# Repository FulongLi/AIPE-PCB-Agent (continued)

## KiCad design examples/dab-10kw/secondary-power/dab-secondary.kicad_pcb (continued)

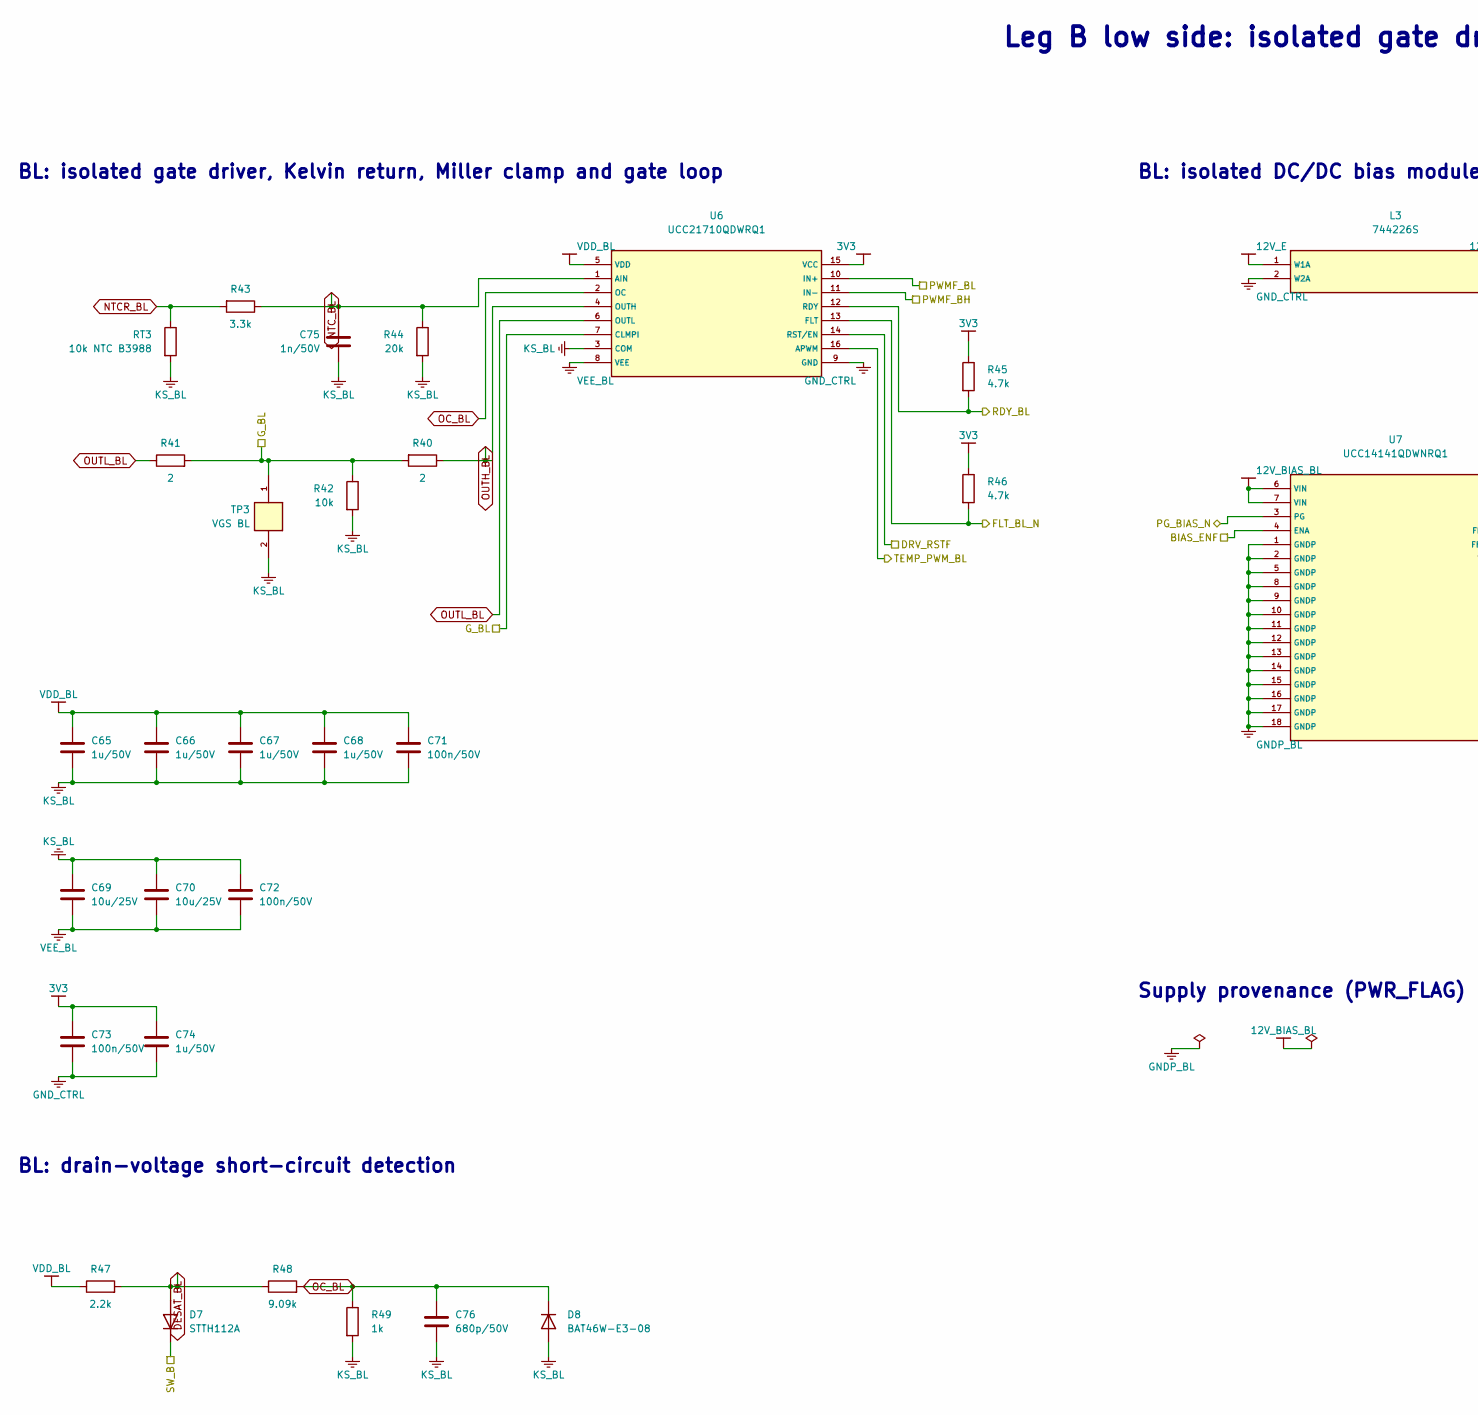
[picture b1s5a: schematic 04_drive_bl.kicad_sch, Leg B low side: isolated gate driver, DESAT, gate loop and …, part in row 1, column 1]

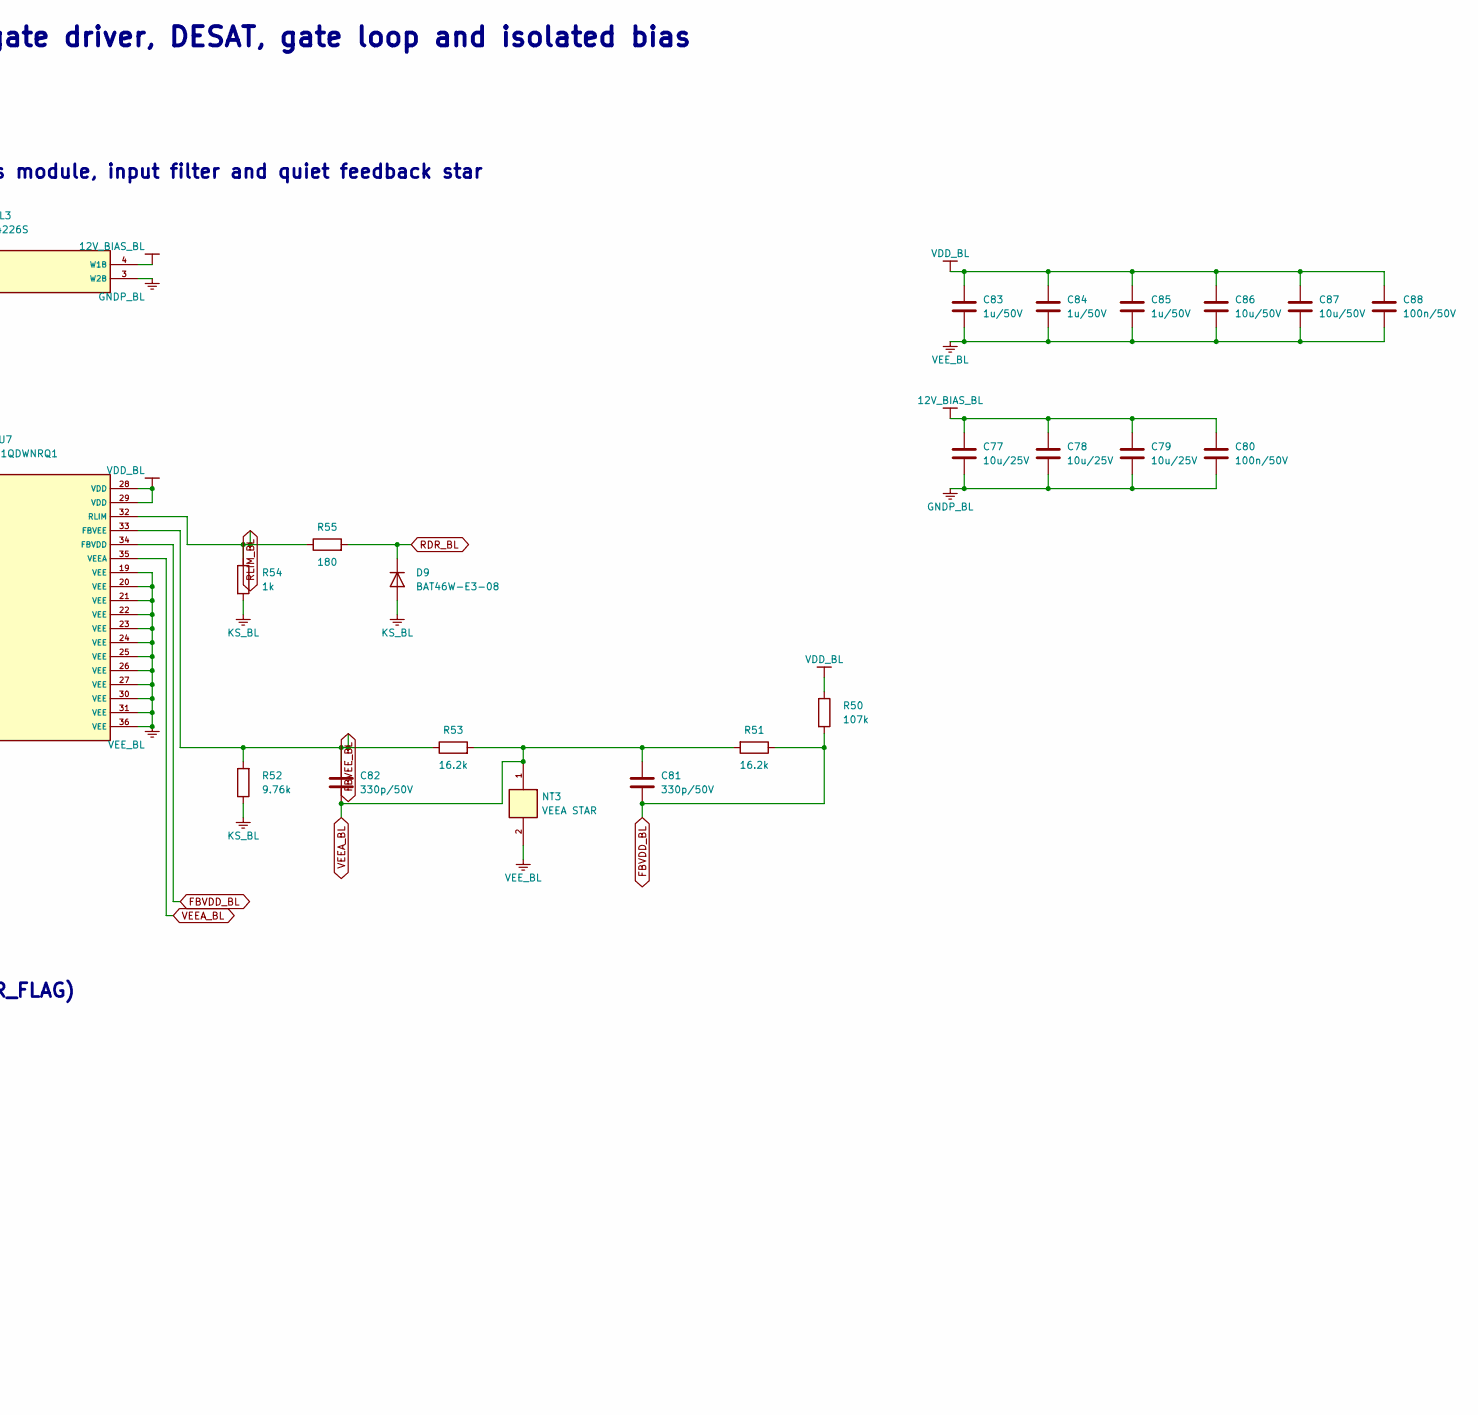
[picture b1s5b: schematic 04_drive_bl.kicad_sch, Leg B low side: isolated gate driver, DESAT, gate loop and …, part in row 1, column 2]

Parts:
C65, C66, C67, C68, C74, C83, C84, C85: 1u/50V; C_0805_2012Metric
C69, C70, C77, C78, C79: 10u/25V; C_1210_3225Metric
C71, C72, C73, C80, C88: 100n/50V; C_0603_1608Metric
C75: 1n/50V; C_0603_1608Metric
C76: 680p/50V; C_0603_1608Metric
C81, C82: 330p/50V; C_0603_1608Metric
C86, C87: 10u/50V; C_1210_3225Metric
D7: STTH112A; D_DO-41_SOD81_P10.16mm_Horizontal
D8, D9: BAT46W-E3-08; D_SOD-123
L3: 744226S; L_CommonMode_Wuerth_WE-SL2
NT3: VEEA STAR; NetTie-2_SMD_Pad0.5mm
R40, R41: 2; R_1206_3216Metric
R42: 10k; R_0805_2012Metric
R43: 3.3k; R_0603_1608Metric
R44: 20k; R_0603_1608Metric
R45, R46: 4.7k; R_0603_1608Metric
R47: 2.2k; R_1206_3216Metric
R48: 9.09k; R_0603_1608Metric
R49: 1k; R_0603_1608Metric
R50: 107k; R_0603_1608Metric
R51, R53: 16.2k; R_0603_1608Metric
R52: 9.76k; R_0603_1608Metric
R54: 1k; R_1206_3216Metric
R55: 180; R_1206_3216Metric
RT3: 10k NTC B3988; R_0805_2012Metric
TP3: VGS BL; TestPoint_2Pads_Pitch2.54mm_Drill0.8mm
U6: UCC21710QDWRQ1; DAB_UCC21710_DW_HV
U7: UCC14141QDWNRQ1; DAB_UCC14141_DWN

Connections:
3V3: C73.1, C74.1, R45.1, R46.1, U6.15 (VCC); also elsewhere on the board
12V_BIAS_BL: C77.1, C78.1, C79.1, C80.1, L3.4 (W1B), U7.6 (VIN), U7.7 (VIN)
12V_E: L3.1 (W1A); also elsewhere on the board
BIAS_ENF: U7.4 (ENA); also elsewhere on the board
DESAT_BL: D7.2 (A), R47.2, R48.1
DRV_RSTF: U6.14 (RST/EN); also elsewhere on the board
FBVDD_BL: C81.1, R50.2, R51.1, U7.34 (FBVDD)
FBVEE_BL: C82.1, R52.2, R53.1, U7.33 (FBVEE)
FLT_BL_N: R46.2, U6.13 (FLT); also elsewhere on the board
GNDP_BL: C77.2, C78.2, C79.2, C80.2, L3.3 (W2B), U7.1 (GNDP), U7.2 (GNDP), U7.5 (GNDP), U7.8 (GNDP), U7.9 (GNDP), U7.10 (GNDP), U7.11 (GNDP), U7.12 (GNDP), U7.13 (GNDP), U7.14 (GNDP), U7.15 (GNDP), U7.16 (GNDP), U7.17 (GNDP), U7.18 (GNDP)
GND_CTRL: C73.2, C74.2, L3.2 (W2A), U6.9 (GND); also elsewhere on the board
G_BL: R40.2, R41.2, R42.1, TP3.1, U6.7 (CLMPI); also elsewhere on the board
KS_BL: C65.2, C66.2, C67.2, C68.2, C69.1, C70.1, C71.2, C72.1, C75.2, C76.2, D8.2 (A), D9.2 (A), R42.2, R44.2, R49.2, R52.1, R54.2, RT3.2, TP3.2, U6.3 (COM); also elsewhere on the board
NTCR_BL: R43.2, RT3.1
NTC_BL: C75.1, R43.1, R44.1, U6.1 (AIN)
OC_BL: C76.1, D8.1 (K), R48.2, R49.1, U6.2 (OC)
OUTH_BL: R40.1, U6.4 (OUTH)
OUTL_BL: R41.1, U6.6 (OUTL)
PG_BIAS_N: U7.3 (PG); also elsewhere on the board
PWMF_BH: U6.11 (IN-); also elsewhere on the board
PWMF_BL: U6.10 (IN+); also elsewhere on the board
RDR_BL: D9.1 (K), R55.2
RDY_BL: R45.2, U6.12 (RDY); also elsewhere on the board
RLIM_BL: R54.1, R55.1, U7.32 (RLIM)
SW_B: D7.1 (K); also elsewhere on the board
TEMP_PWM_BL: U6.16 (APWM); also elsewhere on the board
VDD_BL: C65.1, C66.1, C67.1, C68.1, C71.1, C83.1, C84.1, C85.1, C86.1, C87.1, C88.1, R47.1, R50.1, U6.5 (VDD), U7.28 (VDD), U7.29 (VDD)
VEEA_BL: C81.2, C82.2, NT3.1, R51.2, R53.2, U7.35 (VEEA)
VEE_BL: C69.2, C70.2, C72.2, C83.2, C84.2, C85.2, C86.2, C87.2, C88.2, NT3.2, U6.8 (VEE), U7.19 (VEE), U7.20 (VEE), U7.21 (VEE), U7.22 (VEE), U7.23 (VEE), U7.24 (VEE), U7.25 (VEE), U7.26 (VEE), U7.27 (VEE), U7.30 (VEE), U7.31 (VEE), U7.36 (VEE)

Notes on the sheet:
Leg B low side: isolated gate driver, DESAT, gate loop and isolated bias
BL: isolated gate driver, Kelvin return, Miller clamp and gate loop
BL: drain-voltage short-circuit detection
BL: isolated DC/DC bias module, input filter and quiet feedback star
Supply provenance (PWR_FLAG)

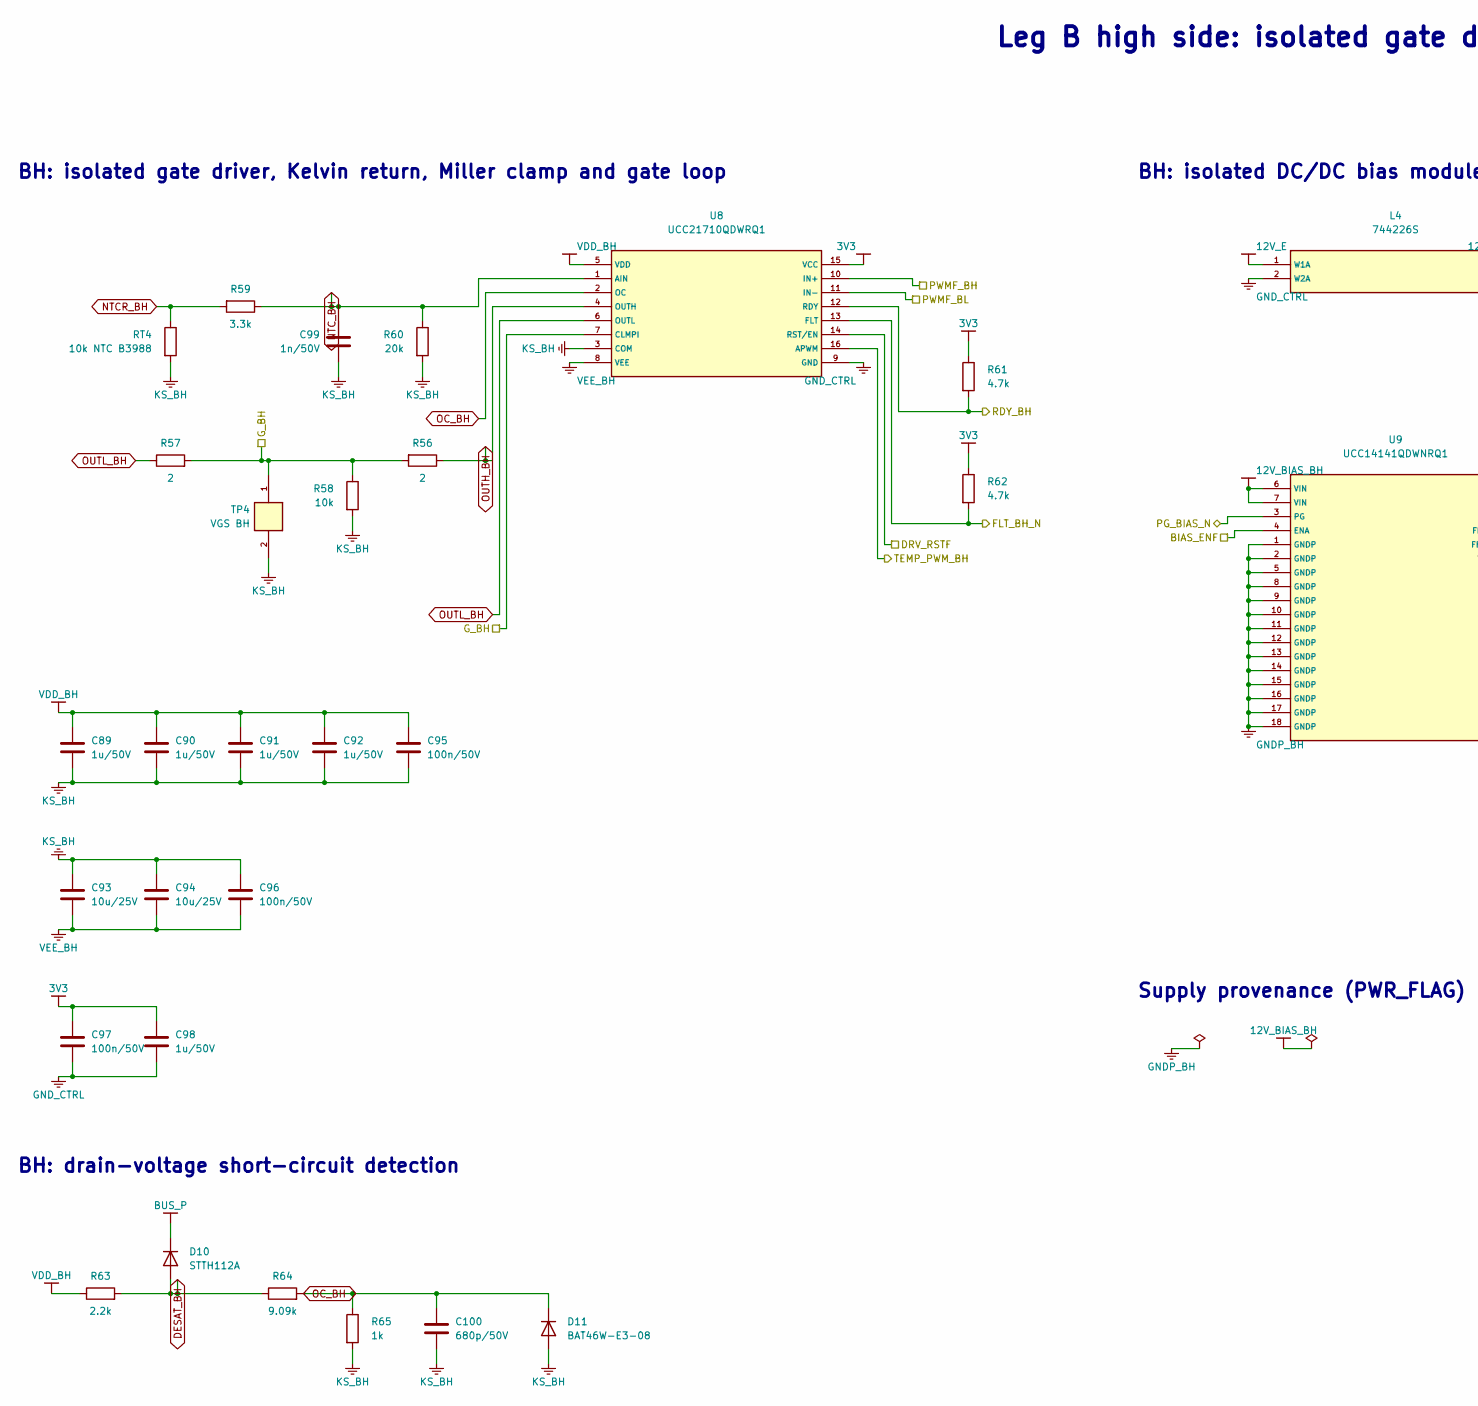
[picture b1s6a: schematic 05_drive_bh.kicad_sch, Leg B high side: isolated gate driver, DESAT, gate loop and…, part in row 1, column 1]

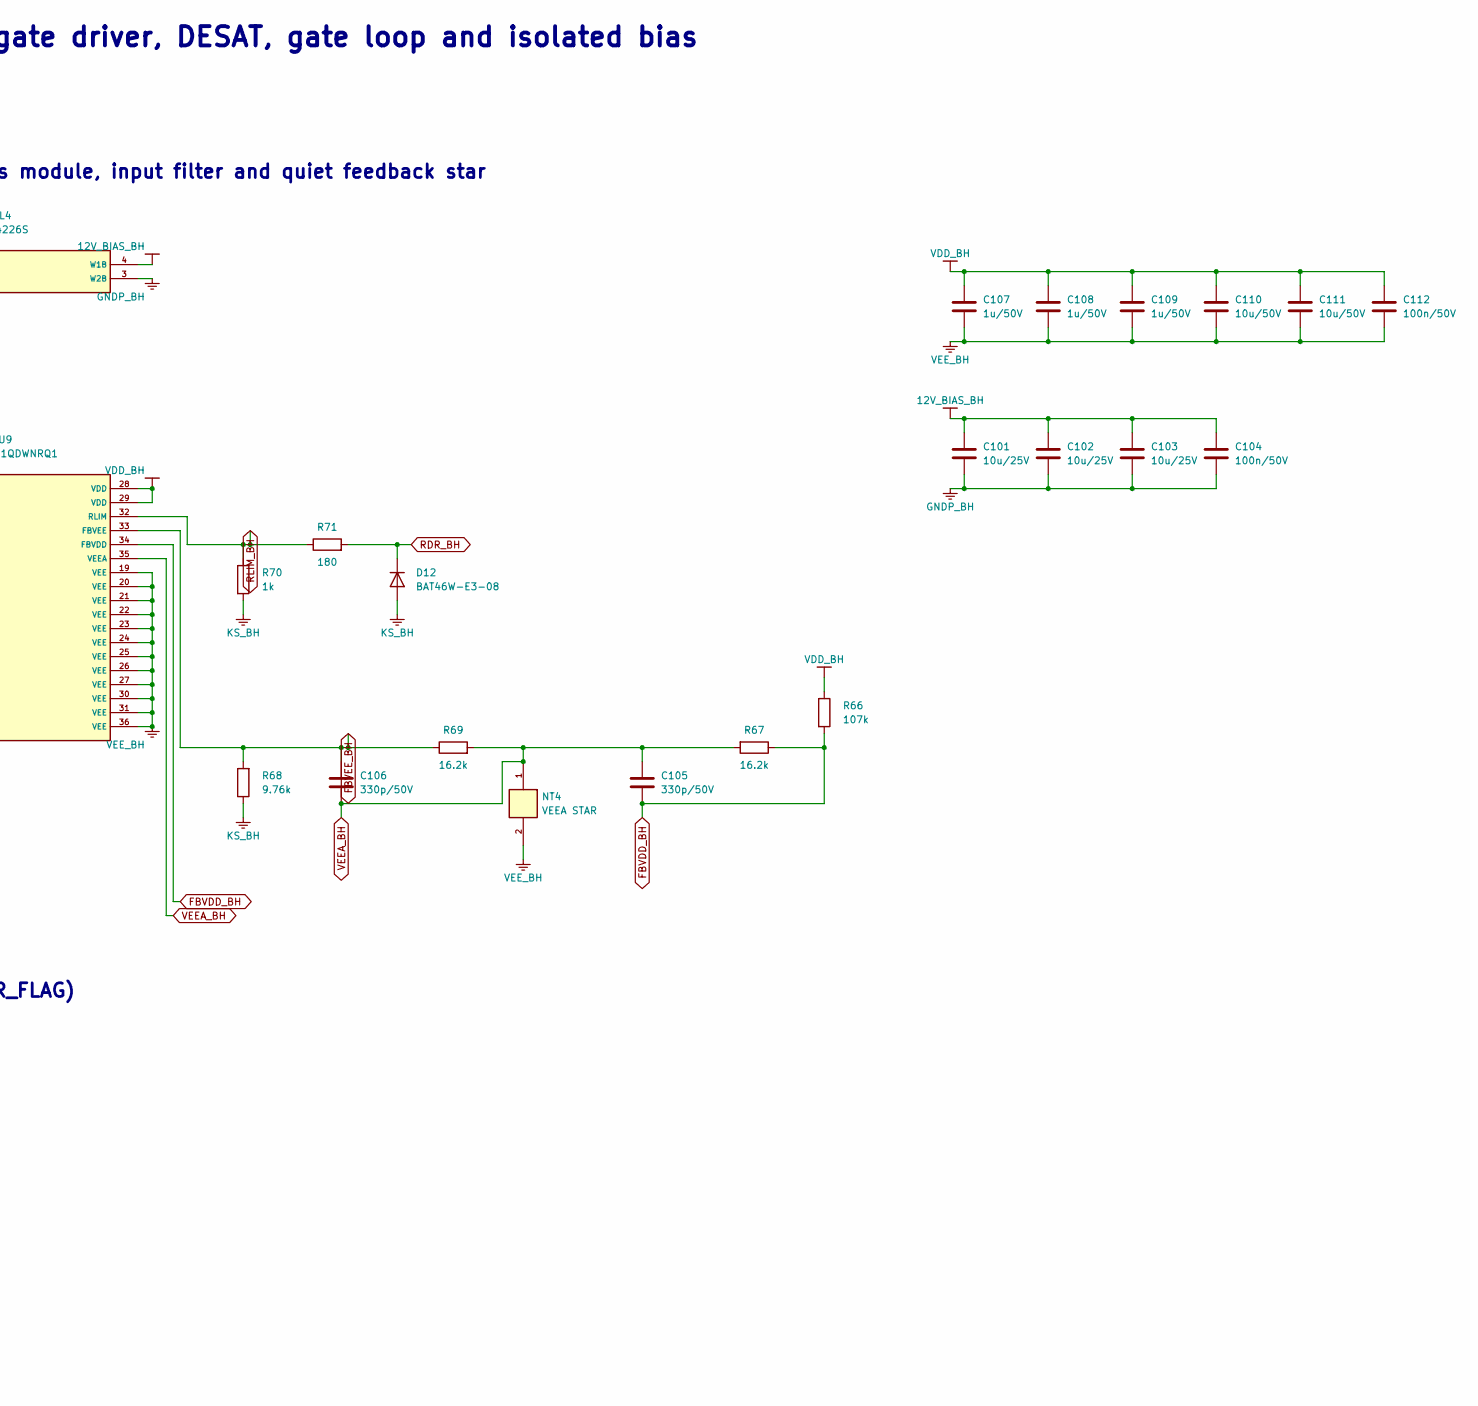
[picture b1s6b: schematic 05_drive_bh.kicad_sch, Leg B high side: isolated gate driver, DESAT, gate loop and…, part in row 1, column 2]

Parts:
C89, C90, C91, C92, C98, C107, C108, C109: 1u/50V; C_0805_2012Metric
C93, C94, C101, C102, C103: 10u/25V; C_1210_3225Metric
C95, C96, C97, C104, C112: 100n/50V; C_0603_1608Metric
C99: 1n/50V; C_0603_1608Metric
C100: 680p/50V; C_0603_1608Metric
C105, C106: 330p/50V; C_0603_1608Metric
C110, C111: 10u/50V; C_1210_3225Metric
D10: STTH112A; D_DO-41_SOD81_P10.16mm_Horizontal
D11, D12: BAT46W-E3-08; D_SOD-123
L4: 744226S; L_CommonMode_Wuerth_WE-SL2
NT4: VEEA STAR; NetTie-2_SMD_Pad0.5mm
R56, R57: 2; R_1206_3216Metric
R58: 10k; R_0805_2012Metric
R59: 3.3k; R_0603_1608Metric
R60: 20k; R_0603_1608Metric
R61, R62: 4.7k; R_0603_1608Metric
R63: 2.2k; R_1206_3216Metric
R64: 9.09k; R_0603_1608Metric
R65: 1k; R_0603_1608Metric
R66: 107k; R_0603_1608Metric
R67, R69: 16.2k; R_0603_1608Metric
R68: 9.76k; R_0603_1608Metric
R70: 1k; R_1206_3216Metric
R71: 180; R_1206_3216Metric
RT4: 10k NTC B3988; R_0805_2012Metric
TP4: VGS BH; TestPoint_2Pads_Pitch2.54mm_Drill0.8mm
U8: UCC21710QDWRQ1; DAB_UCC21710_DW_HV
U9: UCC14141QDWNRQ1; DAB_UCC14141_DWN

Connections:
3V3: C97.1, C98.1, R61.1, R62.1, U8.15 (VCC); also elsewhere on the board
12V_BIAS_BH: C101.1, C102.1, C103.1, C104.1, L4.4 (W1B), U9.6 (VIN), U9.7 (VIN)
12V_E: L4.1 (W1A); also elsewhere on the board
BIAS_ENF: U9.4 (ENA); also elsewhere on the board
BUS_P: D10.1 (K); also elsewhere on the board
DESAT_BH: D10.2 (A), R63.2, R64.1
DRV_RSTF: U8.14 (RST/EN); also elsewhere on the board
FBVDD_BH: C105.1, R66.2, R67.1, U9.34 (FBVDD)
FBVEE_BH: C106.1, R68.2, R69.1, U9.33 (FBVEE)
FLT_BH_N: R62.2, U8.13 (FLT); also elsewhere on the board
GNDP_BH: C101.2, C102.2, C103.2, C104.2, L4.3 (W2B), U9.1 (GNDP), U9.2 (GNDP), U9.5 (GNDP), U9.8 (GNDP), U9.9 (GNDP), U9.10 (GNDP), U9.11 (GNDP), U9.12 (GNDP), U9.13 (GNDP), U9.14 (GNDP), U9.15 (GNDP), U9.16 (GNDP), U9.17 (GNDP), U9.18 (GNDP)
GND_CTRL: C97.2, C98.2, L4.2 (W2A), U8.9 (GND); also elsewhere on the board
G_BH: R56.2, R57.2, R58.1, TP4.1, U8.7 (CLMPI); also elsewhere on the board
KS_BH: C89.2, C90.2, C91.2, C92.2, C93.1, C94.1, C95.2, C96.1, C99.2, C100.2, D11.2 (A), D12.2 (A), R58.2, R60.2, R65.2, R68.1, R70.2, RT4.2, TP4.2, U8.3 (COM); also elsewhere on the board
NTCR_BH: R59.2, RT4.1
NTC_BH: C99.1, R59.1, R60.1, U8.1 (AIN)
OC_BH: C100.1, D11.1 (K), R64.2, R65.1, U8.2 (OC)
OUTH_BH: R56.1, U8.4 (OUTH)
OUTL_BH: R57.1, U8.6 (OUTL)
PG_BIAS_N: U9.3 (PG); also elsewhere on the board
PWMF_BH: U8.10 (IN+); also elsewhere on the board
PWMF_BL: U8.11 (IN-); also elsewhere on the board
RDR_BH: D12.1 (K), R71.2
RDY_BH: R61.2, U8.12 (RDY); also elsewhere on the board
RLIM_BH: R70.1, R71.1, U9.32 (RLIM)
TEMP_PWM_BH: U8.16 (APWM); also elsewhere on the board
VDD_BH: C89.1, C90.1, C91.1, C92.1, C95.1, C107.1, C108.1, C109.1, C110.1, C111.1, C112.1, R63.1, R66.1, U8.5 (VDD), U9.28 (VDD), U9.29 (VDD)
VEEA_BH: C105.2, C106.2, NT4.1, R67.2, R69.2, U9.35 (VEEA)
VEE_BH: C93.2, C94.2, C96.2, C107.2, C108.2, C109.2, C110.2, C111.2, C112.2, NT4.2, U8.8 (VEE), U9.19 (VEE), U9.20 (VEE), U9.21 (VEE), U9.22 (VEE), U9.23 (VEE), U9.24 (VEE), U9.25 (VEE), U9.26 (VEE), U9.27 (VEE), U9.30 (VEE), U9.31 (VEE), U9.36 (VEE)

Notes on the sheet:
Leg B high side: isolated gate driver, DESAT, gate loop and isolated bias
BH: isolated gate driver, Kelvin return, Miller clamp and gate loop
BH: drain-voltage short-circuit detection
BH: isolated DC/DC bias module, input filter and quiet feedback star
Supply provenance (PWR_FLAG)

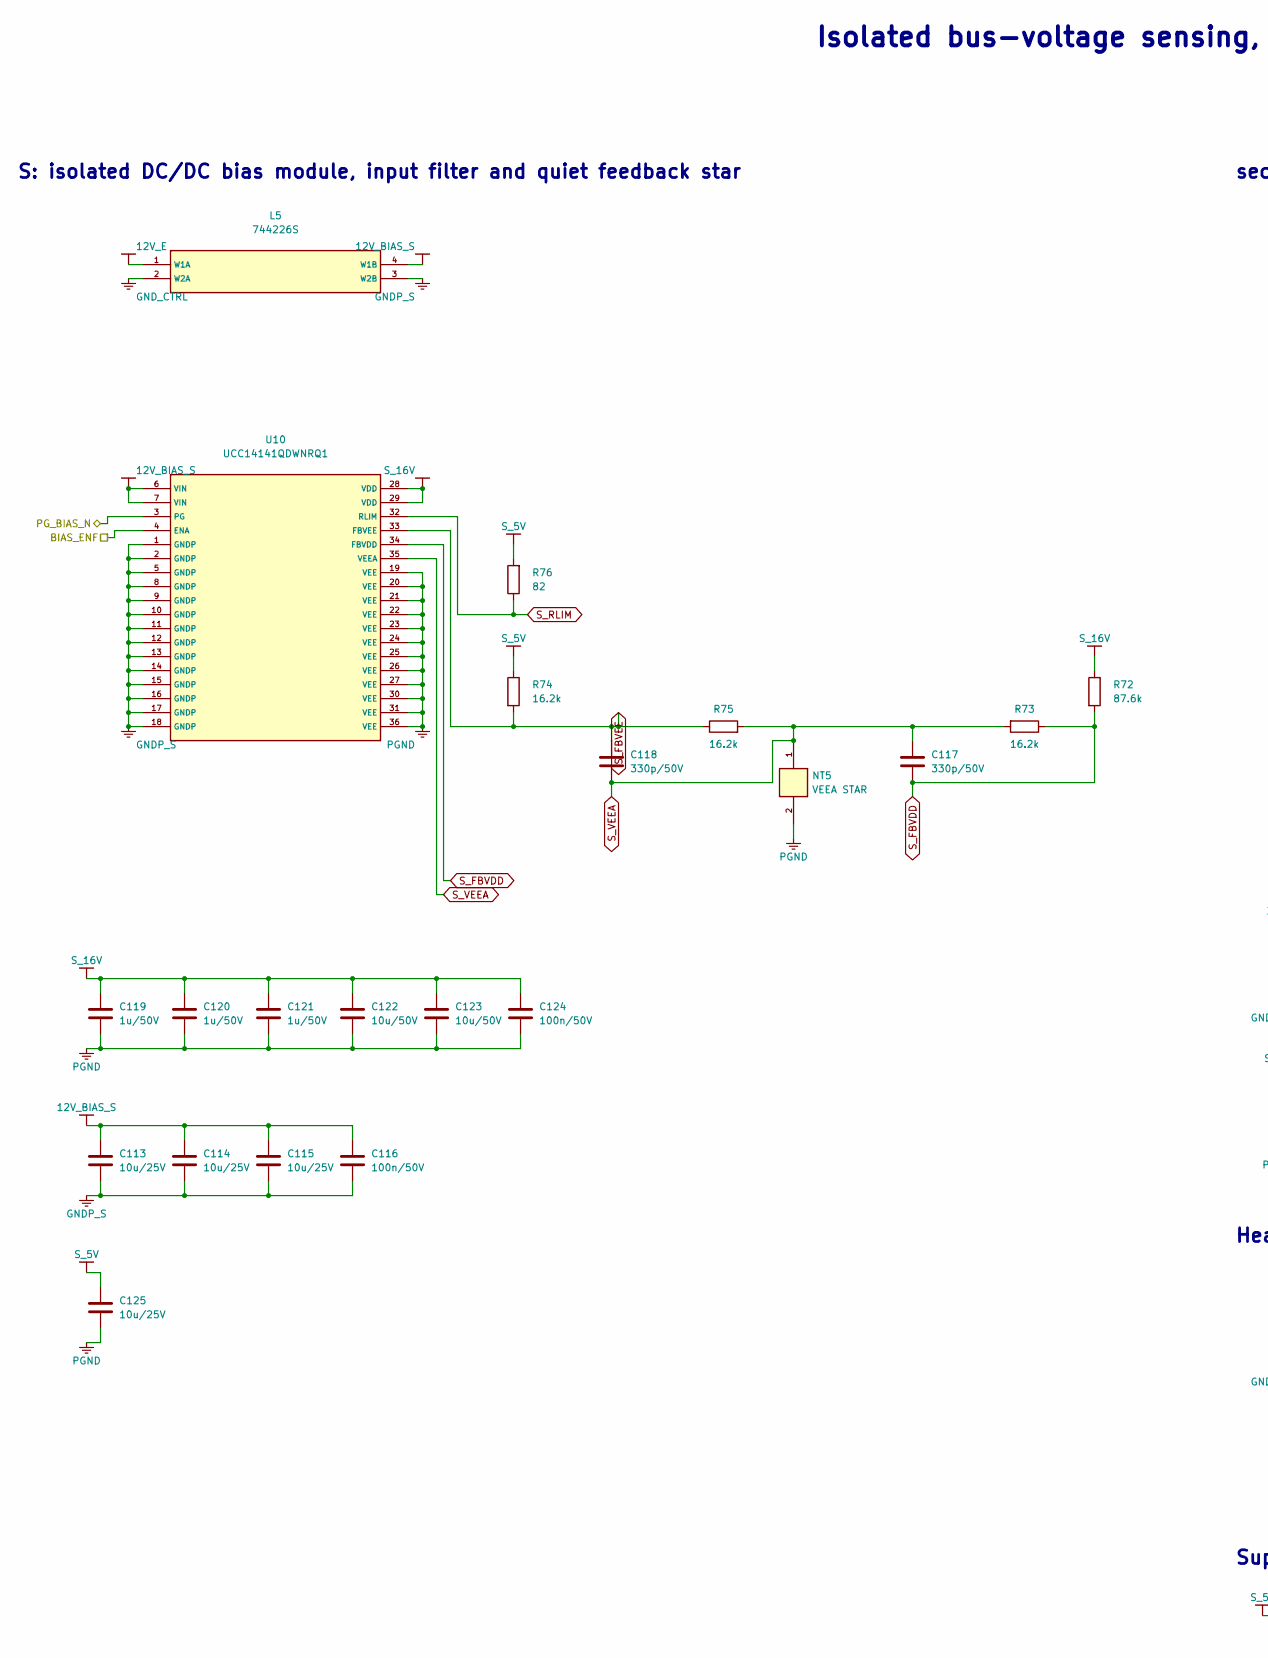
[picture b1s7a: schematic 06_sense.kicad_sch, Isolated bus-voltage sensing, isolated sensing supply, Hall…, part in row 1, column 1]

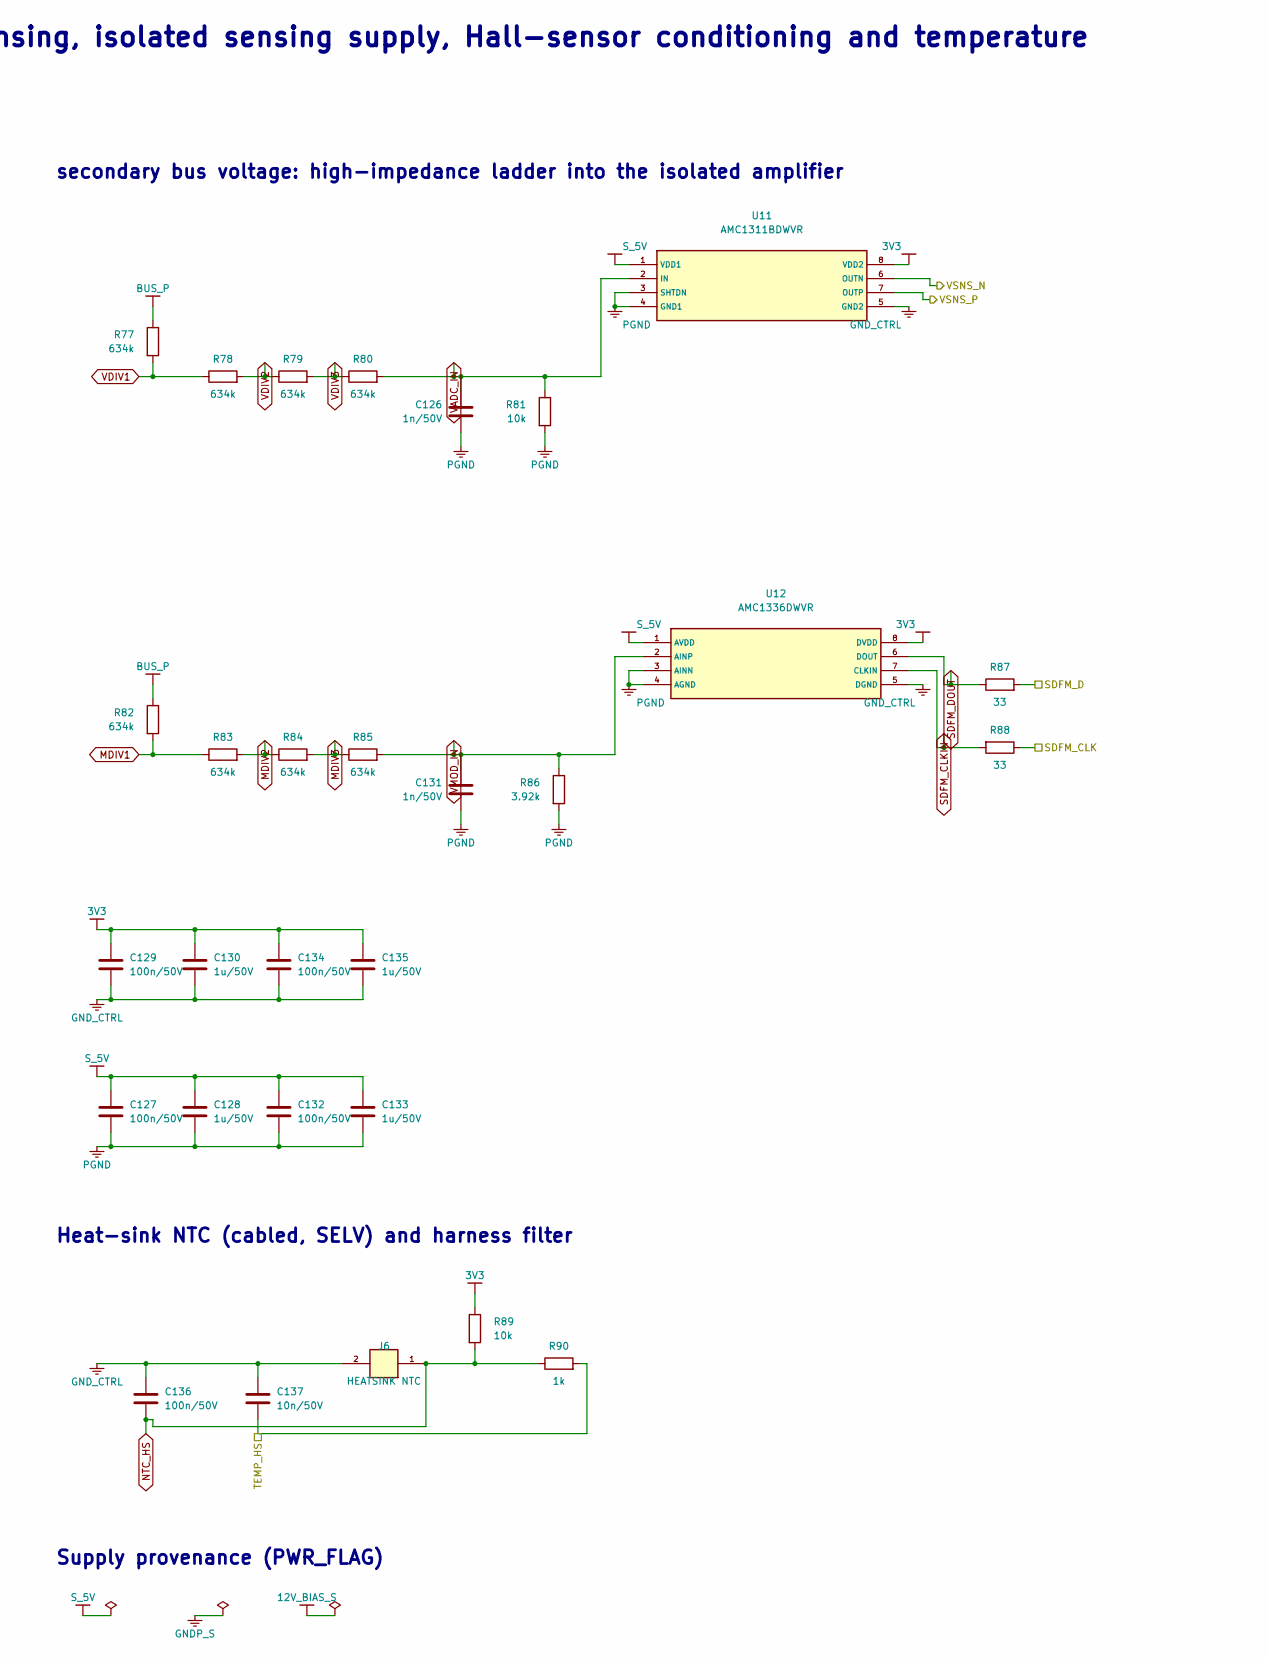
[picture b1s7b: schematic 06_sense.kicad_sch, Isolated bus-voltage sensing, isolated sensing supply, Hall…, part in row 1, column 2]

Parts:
C113, C114, C115, C125: 10u/25V; C_1210_3225Metric
C116, C124, C127, C129, C132, C134, C136: 100n/50V; C_0603_1608Metric
C117, C118: 330p/50V; C_0603_1608Metric
C119, C120, C121, C128, C130, C133, C135: 1u/50V; C_0805_2012Metric
C122, C123: 10u/50V; C_1210_3225Metric
C126, C131: 1n/50V; C_0603_1608Metric
C137: 10n/50V; C_0603_1608Metric
J6: HEATSINK NTC; JST_PH_B2B-PH-K_1x02_P2.00mm_Vertical
L5: 744226S; L_CommonMode_Wuerth_WE-SL2
NT5: VEEA STAR; NetTie-2_SMD_Pad0.5mm
R72: 87.6k; R_0603_1608Metric
R73, R74, R75: 16.2k; R_0603_1608Metric
R76: 82; R_1206_3216Metric
R77, R78, R79, R80, R82, R83, R84, R85: 634k; R_1206_3216Metric
R81, R89: 10k; R_0603_1608Metric
R86: 3.92k; R_0603_1608Metric
R87, R88: 33; R_0603_1608Metric
R90: 1k; R_0603_1608Metric
U10: UCC14141QDWNRQ1; DAB_UCC14141_DWN
U11: AMC1311BDWVR; DAB_AMC1311_DWV
U12: AMC1336DWVR; DAB_AMC1336_DWV

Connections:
3V3: C129.1, C130.1, C134.1, C135.1, R89.1, U11.8 (VDD2), U12.8 (DVDD); also elsewhere on the board
12V_BIAS_S: C113.1, C114.1, C115.1, C116.1, L5.4 (W1B), U10.6 (VIN), U10.7 (VIN)
12V_E: L5.1 (W1A); also elsewhere on the board
BIAS_ENF: U10.4 (ENA); also elsewhere on the board
BUS_P: R77.1, R82.1; also elsewhere on the board
GNDP_S: C113.2, C114.2, C115.2, C116.2, L5.3 (W2B), U10.1 (GNDP), U10.2 (GNDP), U10.5 (GNDP), U10.8 (GNDP), U10.9 (GNDP), U10.10 (GNDP), U10.11 (GNDP), U10.12 (GNDP), U10.13 (GNDP), U10.14 (GNDP), U10.15 (GNDP), U10.16 (GNDP), U10.17 (GNDP), U10.18 (GNDP)
GND_CTRL: C129.2, C130.2, C134.2, C135.2, C136.2, C137.2, J6.2, L5.2 (W2A), U11.5 (GND2), U12.5 (DGND); also elsewhere on the board
MDIV1: R82.2, R83.1
MDIV2: R83.2, R84.1
MDIV3: R84.2, R85.1
NTC_HS: C136.1, J6.1, R89.2, R90.1
PGND: C119.2, C120.2, C121.2, C122.2, C123.2, C124.2, C125.2, C126.2, C127.2, C128.2, C131.2, C132.2, C133.2, NT5.2, R81.2, R86.2, U10.19 (VEE), U10.20 (VEE), U10.21 (VEE), U10.22 (VEE), U10.23 (VEE), U10.24 (VEE), U10.25 (VEE), U10.26 (VEE), U10.27 (VEE), U10.30 (VEE), U10.31 (VEE), U10.36 (VEE), U11.3 (SHTDN), U11.4 (GND1), U12.3 (AINN), U12.4 (AGND); also elsewhere on the board
PG_BIAS_N: U10.3 (PG); also elsewhere on the board
SDFM_CLK: R88.1; also elsewhere on the board
SDFM_CLKIN: R88.2, U12.7 (CLKIN)
SDFM_D: R87.2; also elsewhere on the board
SDFM_DOUT: R87.1, U12.6 (DOUT)
S_5V: C125.1, C127.1, C128.1, C132.1, C133.1, R74.1, R76.2, U11.1 (VDD1), U12.1 (AVDD)
S_16V: C119.1, C120.1, C121.1, C122.1, C123.1, C124.1, R72.1, U10.28 (VDD), U10.29 (VDD)
S_FBVDD: C117.1, R72.2, R73.1, U10.34 (FBVDD)
S_FBVEE: C118.1, R74.2, R75.1, U10.33 (FBVEE)
S_RLIM: R76.1, U10.32 (RLIM)
S_VEEA: C117.2, C118.2, NT5.1, R73.2, R75.2, U10.35 (VEEA)
TEMP_HS: C137.1, R90.2; also elsewhere on the board
VADC_IN: C126.1, R80.2, R81.1, U11.2 (IN)
VDIV1: R77.2, R78.1
VDIV2: R78.2, R79.1
VDIV3: R79.2, R80.1
VMOD_IN: C131.1, R85.2, R86.1, U12.2 (AINP)
VSNS_N: U11.6 (OUTN); also elsewhere on the board
VSNS_P: U11.7 (OUTP); also elsewhere on the board

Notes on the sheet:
Isolated bus-voltage sensing, isolated sensing supply, Hall-sensor conditioning and temperature
S: isolated DC/DC bias module, input filter and quiet feedback star
secondary bus voltage: high-impedance ladder into the isolated amplifier
Heat-sink NTC (cabled, SELV) and harness filter
Supply provenance (PWR_FLAG)
